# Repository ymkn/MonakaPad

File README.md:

# MonakaPad

Tadpole Pinマウントやスクリューレス機構などを試すためのマクロパッド

## ビルドガイド

[doc/buildguide.md](doc/buildguide.md)

## LICENSE

This project is licensed under the MIT License, see the [LICENSE file](LICENSE) for details.

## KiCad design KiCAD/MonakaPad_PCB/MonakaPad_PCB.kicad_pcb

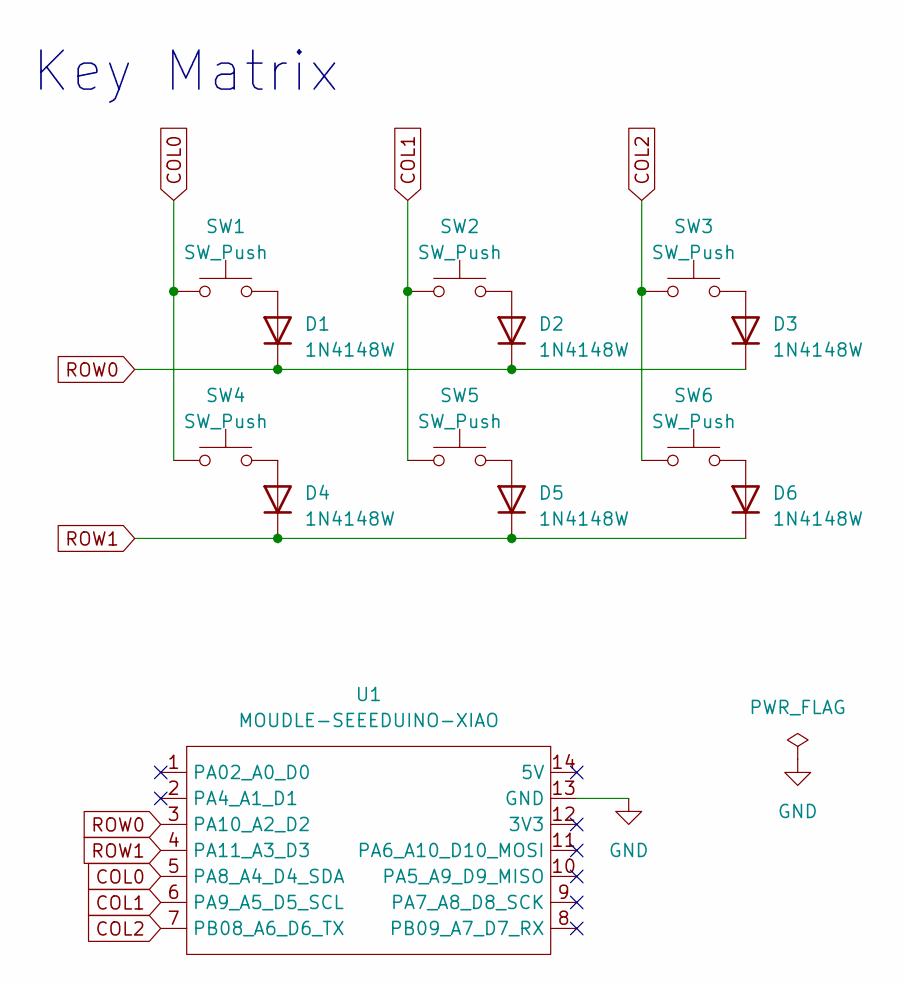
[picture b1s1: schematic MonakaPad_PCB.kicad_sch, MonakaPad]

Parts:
D1, D2, D3, D4, D5, D6: 1N4148W; D_SOD-123; LCSC Parts # C81598
SW1, SW2, SW3, SW4, SW5, SW6: SW_Push; SW_Hotswap_Kailh_MX_1.00u
U1: MOUDLE-SEEEDUINO-XIAO; MOUDLE14P-2.54-21X17.8MM

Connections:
COL0: SW1.1, SW4.1, U1.5 (PA8_A4_D4_SDA); also elsewhere on the board
COL1: SW2.1, SW5.1, U1.6 (PA9_A5_D5_SCL); also elsewhere on the board
COL2: SW3.1, SW6.1, U1.7 (PB08_A6_D6_TX); also elsewhere on the board
unnamed: D1.2 (A), SW1.2
unnamed: D2.2 (A), SW2.2
unnamed: D3.2 (A), SW3.2
unnamed: D4.2 (A), SW4.2
unnamed: D5.2 (A), SW5.2
unnamed: D6.2 (A), SW6.2
ROW0: D1.1 (K), D2.1 (K), D3.1 (K), U1.3 (PA10_A2_D2); also elsewhere on the board
ROW1: D4.1 (K), D5.1 (K), D6.1 (K), U1.4 (PA11_A3_D3); also elsewhere on the board

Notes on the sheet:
Key Matrix

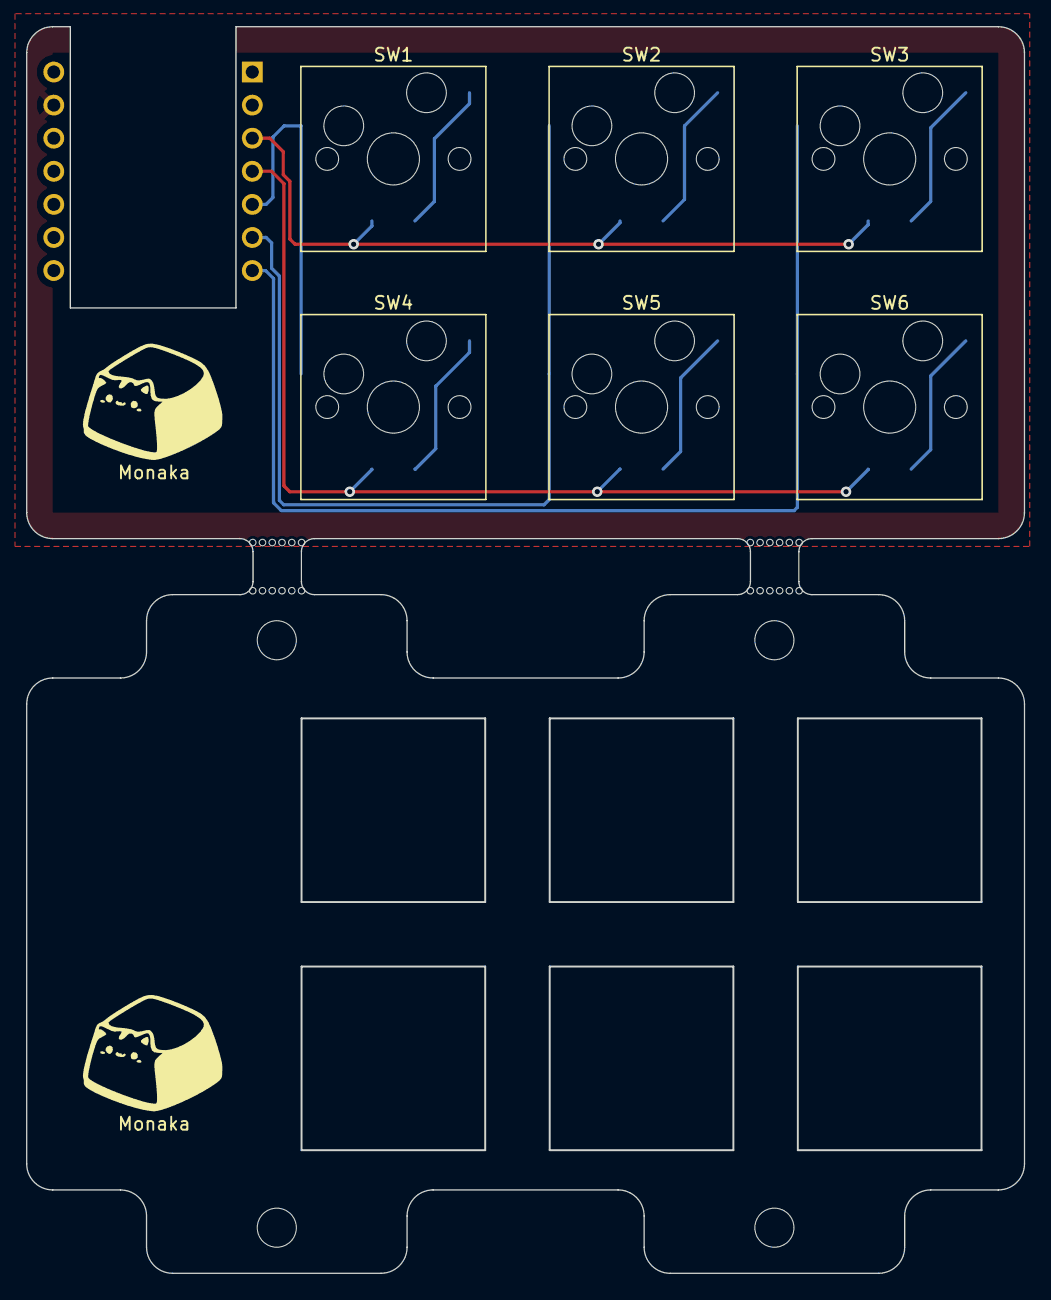
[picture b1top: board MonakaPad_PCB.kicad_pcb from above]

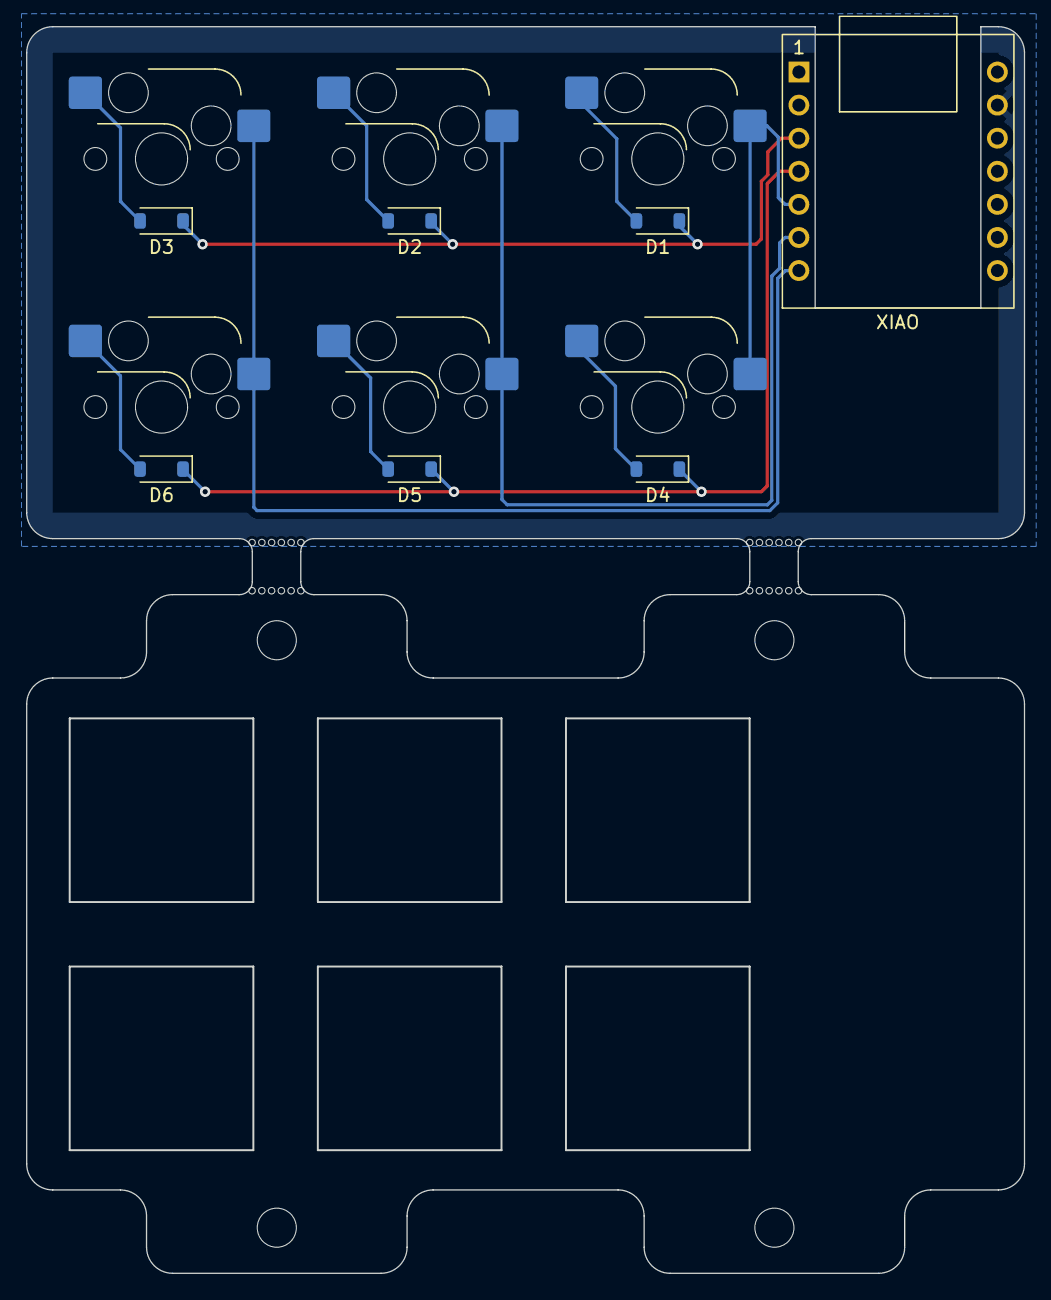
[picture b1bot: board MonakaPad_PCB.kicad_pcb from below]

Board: 2 copper layers, 76.6 x 95.7 mm, 23 parts (7 on the bottom side), 11 nets.

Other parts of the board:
Ref**: Val**; Mouse_Bite_Hole
Ref**#2, Ref**#3, Ref**#4: Val**; Mouse_Bite_Hole
SW1-Hole, SW2-Hole, SW3-Hole, SW4-Hole, SW5-Hole, SW6-Hole: SW_Push; SW_Hole_1u_JLC
XIAO: MOUDLE-SEEEDUINO-XIAO; MOUDLE14P-2.54-21X17.8MM

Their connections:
COL0: XIAO.5 (PA8_A4_D4_SDA); also elsewhere on the board
COL1: XIAO.6 (PA9_A5_D5_SCL); also elsewhere on the board
COL2: XIAO.7 (PB08_A6_D6_TX); also elsewhere on the board
ROW0: XIAO.3 (PA10_A2_D2); also elsewhere on the board
ROW1: XIAO.4 (PA11_A3_D3); also elsewhere on the board

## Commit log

2024-05-02 リンクの修正
2024-05-02 項番のズレを修正
2024-05-02 誤字の修正
